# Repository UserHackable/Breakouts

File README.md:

## Breakouts

A bunch of random breakout boards
## 4ButtonBreakout 

### Board dimensions

* (165000, 125000) original units
* (1.6500, 1.2500) inches
* (41.9100, 31.7500) mm

[gerbers](4ButtonBreakout_gerber.zip?raw=true)

| Front | Back |
| --- | --- |
|  |  |

## 5MMHexaStellaBreakout 

### Board dimensions

* (100000, 100000) original units
* (1.0000, 1.0000) inches
* (25.4000, 25.4000) mm

[gerbers](5MMHexaStellaBreakout_gerber.zip?raw=true)

| Front | Back |
| --- | --- |
|  |  |

## Joystick 

### Board dimensions

* (110000, 125000) original units
* (1.1000, 1.2500) inches
* (27.9400, 31.7500) mm

[gerbers](Joystick_gerber.zip?raw=true)

| Front | Back |
| --- | --- |
|  |  |

## Led_Bar 

### Board dimensions

* (150000, 45000) original units
* (1.5000, 0.4500) inches
* (38.1000, 11.4300) mm

[gerbers](Led_Bar_gerber.zip?raw=true)

| Front | Back |
| --- | --- |
|  |  |

## MinimalDigitalAmp 

### Board dimensions

* (100000, 69994) original units
* (1.0000, 0.6999) inches
* (25.4000, 17.7785) mm

[gerbers](MinimalDigitalAmp_gerber.zip?raw=true)

| Front | Back |
| --- | --- |
|  |  |

## SingleToggleBreakout 

### Board dimensions

* (60000, 64993) original units
* (0.6000, 0.6499) inches
* (15.2400, 16.5082) mm

[gerbers](SingleToggleBreakout_gerber.zip?raw=true)

| Front | Back |
| --- | --- |
|  |  |

## UsbA 

### Board dimensions

* (99951, 47461) original units
* (0.9995, 0.4746) inches
* (25.3876, 12.0551) mm

[gerbers](UsbA_gerber.zip?raw=true)

| Front | Back |
| --- | --- |
|  |  |

## USBMiniBPower 

### Board dimensions

* (70000, 50000) original units
* (0.7000, 0.5000) inches
* (17.7800, 12.7000) mm

[gerbers](USBMiniBPower_gerber.zip?raw=true)

| Front | Back |
| --- | --- |
|  |  |

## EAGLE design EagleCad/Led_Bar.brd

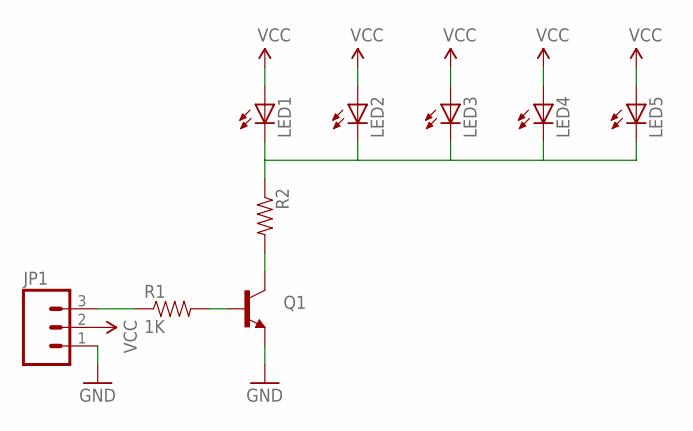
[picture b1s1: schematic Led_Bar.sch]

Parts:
JP1: M03PTH; 1X03
LED1, LED2, LED3, LED4, LED5: LED5MM
Q1: TRANSISTOR_NPNTO-92-AMMO; TO-92-AMMO
R1: 1K; AXIAL-0.3
R2: RESISTORAXIAL-0.3; AXIAL-0.3

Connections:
GND: JP1.1, Q1.1 (E)
unnamed: Q1.2 (B), R1.P$2 (2)
unnamed: JP1.3, R1.P$1 (1)
unnamed: Q1.3 (C), R2.P$2 (2)
unnamed: LED1.K (C), LED2.K (C), LED3.K (C), LED4.K (C), LED5.K (C), R2.P$1 (1)
VCC: JP1.2, LED1.A, LED2.A, LED3.A, LED4.A, LED5.A

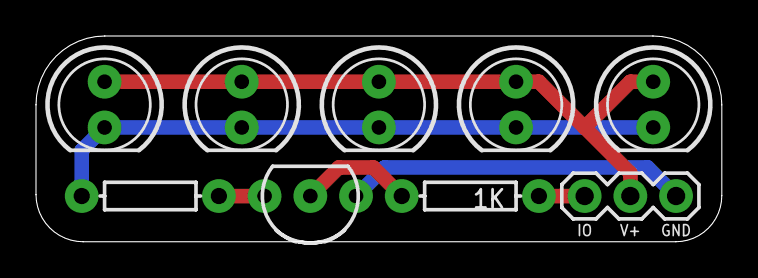
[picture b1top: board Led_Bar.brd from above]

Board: 2 copper layers, 38.1 x 11.4 mm, 9 parts (0 on the bottom side), 6 nets.

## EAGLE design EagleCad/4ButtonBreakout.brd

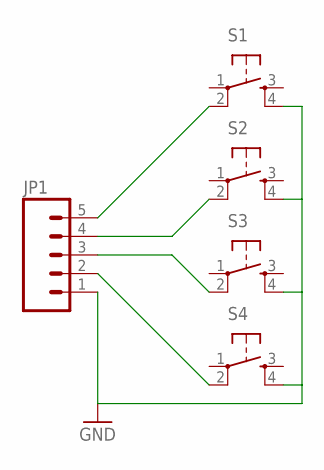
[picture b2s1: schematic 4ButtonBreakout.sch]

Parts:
JP1: M05PTH; 1X05
S1, S2, S3, S4: TAC_SWITCH12MM; B3F_10

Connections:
GND: JP1.1, S1.4, S2.4, S3.4, S4.4
unnamed: JP1.5, S1.2
unnamed: JP1.4, S2.2
unnamed: JP1.3, S3.2
unnamed: JP1.2, S4.2

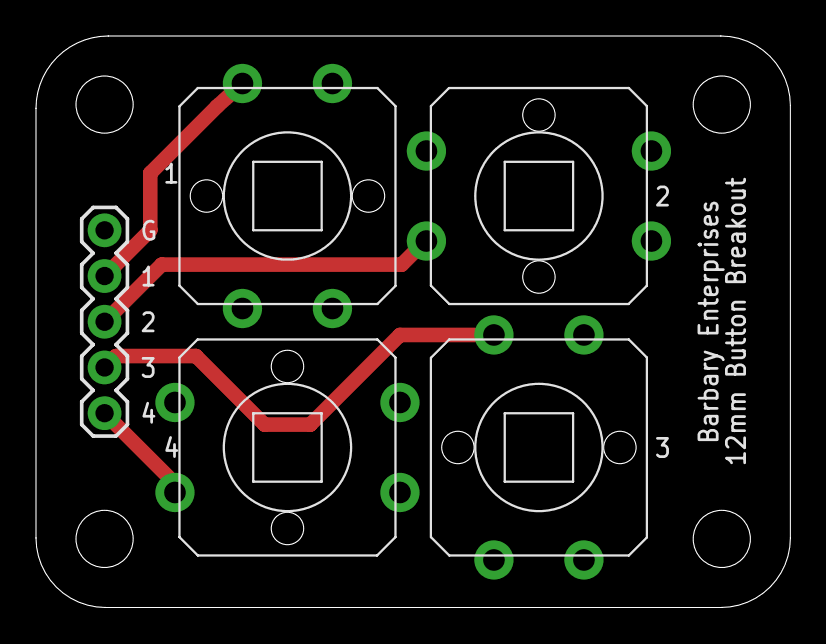
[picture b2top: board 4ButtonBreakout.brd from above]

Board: 2 copper layers, 41.9 x 31.8 mm, 5 parts (0 on the bottom side), 5 nets.

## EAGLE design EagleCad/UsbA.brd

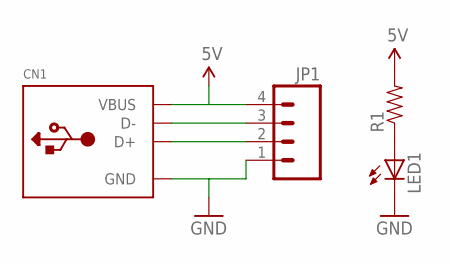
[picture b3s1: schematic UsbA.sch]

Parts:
CN1: USB_TYPEAPCB; USBA_PCB
JP1: M04PTH; 1X04
LED1: LED5MM
R1: RESISTORAXIAL-0.3; AXIAL-0.3

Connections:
5V: CN1.VCC (VBUS), JP1.4, R1.P$2 (2)
D+: CN1.USB_PLUS (D+), JP1.2
D-: CN1.USB_NEG (D-), JP1.3
GND: CN1.GND, JP1.1, LED1.K (C)
unnamed: LED1.A, R1.P$1 (1)

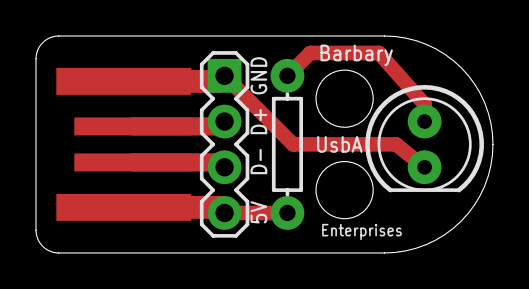
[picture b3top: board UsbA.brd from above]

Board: 2 copper layers, 25.4 x 12.1 mm, 4 parts (0 on the bottom side), 5 nets.

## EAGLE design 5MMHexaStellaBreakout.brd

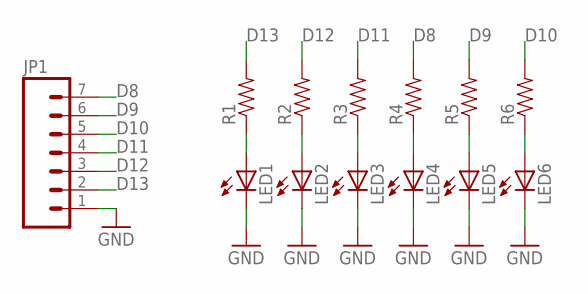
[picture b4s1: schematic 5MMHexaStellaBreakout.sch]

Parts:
JP1: M07; 1X07
LED1, LED2, LED3, LED4, LED5, LED6: LED5MM
R1, R2, R3, R4, R5, R6: RESISTORAXIAL-0.3; AXIAL-0.3

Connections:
D8: JP1.7, R4.P$2 (2)
D9: JP1.6, R5.P$2 (2)
D10: JP1.5, R6.P$2 (2)
D11: JP1.4, R3.P$2 (2)
D12: JP1.3, R2.P$2 (2)
D13: JP1.2, R1.P$2 (2)
GND: JP1.1, LED1.K (C), LED2.K (C), LED3.K (C), LED4.K (C), LED5.K (C), LED6.K (C)
unnamed: LED1.A, R1.P$1 (1)
unnamed: LED4.A, R4.P$1 (1)
unnamed: LED2.A, R2.P$1 (1)
unnamed: LED5.A, R5.P$1 (1)
unnamed: LED3.A, R3.P$1 (1)
unnamed: LED6.A, R6.P$1 (1)

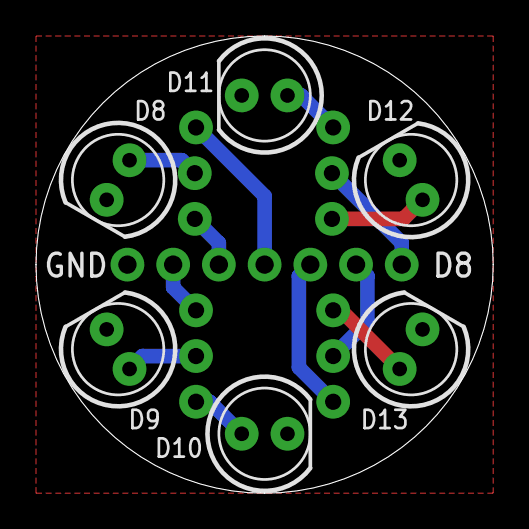
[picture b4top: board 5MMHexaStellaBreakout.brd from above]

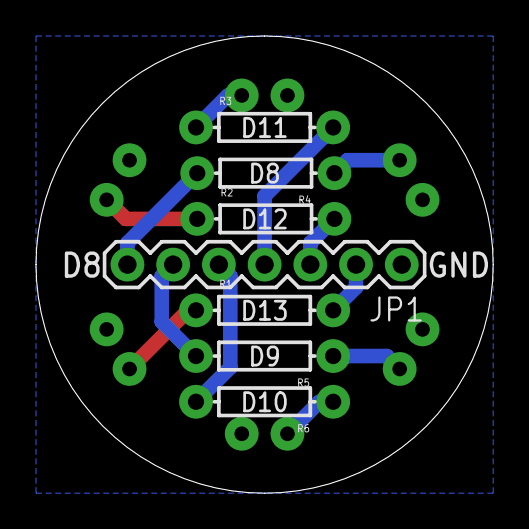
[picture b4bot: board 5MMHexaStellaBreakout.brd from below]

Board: 2 copper layers, 25.4 x 25.4 mm, 13 parts (7 on the bottom side), 13 nets.

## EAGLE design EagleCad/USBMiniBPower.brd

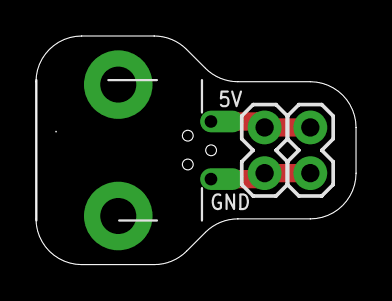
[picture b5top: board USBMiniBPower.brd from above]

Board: 2 copper layers, 17.8 x 12.7 mm, 3 parts (0 on the bottom side), 2 nets.

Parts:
JP1, JP2: M02PTH; 1X02
U$1: USB-PWR; USB-MINIB-THM-MOLEX-PWRONLY

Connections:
5V: JP1.2, JP2.2, U$1.VBUS
GND: JP1.1, JP2.1, U$1.GND

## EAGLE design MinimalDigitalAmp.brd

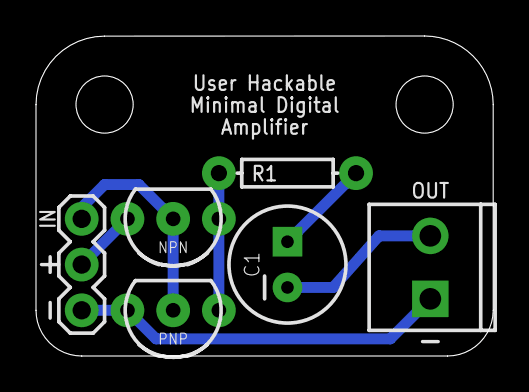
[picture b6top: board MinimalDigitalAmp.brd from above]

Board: 2 copper layers, 25.4 x 17.8 mm, 6 parts (0 on the bottom side), 6 nets.

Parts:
C1: CPOL-RADIAL-100UF-25V
JP1: 1X03
JP2: M023.5MM; SCREWTERMINAL-3.5MM-2
NPN: TO-92-AMMO
PNP: TO-92-AMMO
R1: AXIAL-0.3

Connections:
GND: JP1.1, JP2.1, PNP.3
unnamed: C1.1, R1.P$2
unnamed: C1.2, JP2.2
unnamed: JP1.3, NPN.2, PNP.2
unnamed: NPN.1, PNP.1, R1.P$1
VCC: JP1.2, NPN.3

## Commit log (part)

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2016-04-08 from Makefile
2016-04-08 cleaning out temps

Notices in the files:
parts and their libraries:
SparkFun-Connectors: Licensing: Creative Commons ShareAlike 4.0 International - https://creativecommons.org/licenses/by-sa/4.0
